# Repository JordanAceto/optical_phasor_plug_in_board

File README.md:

# NOTE: development of all VCF plug-in boards has been moved here https://github.com/JordanAceto/VCF_plug_in_boards

### This repo will no longer be updated. Follow the above link for the most current files.

# Optical Phasor Plug-In Board

Small 6 stage optical phase shifter PCB, designed to plug into a larger motherboard.

## Details

The main circuit is based on the famous Mutron phasor circuit with the addition of voltage controlled feedback. This PCB includes the audio path and CV inputs for frequency and feedback, but does not include any modulation sources.

The intended use for this board is to plug in to a larger motherboard which contains slots for two of these phasor boards, as well as modulation sources, panel controls, and input/output routing. This motherboard could accept different filter boards sharing this footprint and header layout, for realizing stereo effects of various flavors.

## Inputs

-Audio in: dry audio input to be phase shifted.

-Frequency CV in: 0 volts to +2.048 volts, higher voltage = higher sweep.

-Feedback CV in: 0 volts to +2.048 volts, higher voltage = more feedback.

## Outputs

-Audio out: phase shifted audio output.

## Power Supply Requirements

A bipolar 12 volt power supply capable of supplying 50mA is needed. This will typically come from the motherboard.

## Note About The Light Dependent Resistors

Low on resistance and high off resistance are desirable if a wide sweep range is wanted. Slow/fast response is up to personal taste.

The choice of LED has a large impact on sweep depth. Diffused green LEDs were found to produce good results, but feel free to experiment.

The LED and surrounding LDRs should be protected from ambient light under an opaque cover.

## Calibration

-RV1 (depth trim): trims the depth of incoming frequency CV signals. Turn CW for greater depth and CCW for less depth. Adjust to taste.

-RV2 (center trim): trims the center frequency of the phase shifter. Turn CW for higher center frequency and CCW for lower center frequency. Adjust to taste.

-RV3 (feedback trim): trims the maximum amount of feedback. Turn CW for more maximum feedback and CCW for less maximum feedback. Exercise caution when adjusting this, as extreme settings can result in loud oscillations which could damage your ears or speakers if you are monitoring the sound with a loud amplifier. If you set this trimmer to be right on the edge of oscillation when about +2 volts is applied to the feedback CV input then make sure to sweep the frequency through its entire range, as a setting that doesn't squeal at certain frequency settings may squeal at other settings.

## Parts Ordering
The BOM has a link to a Mouser project with the majority of the parts needed to build the board, with the exception of the LDRs. There is a link to the SmallBear Electronics parts page for their LDRs, which were found to work well. Feel free to experiment with different LDRs.

The BOM also has a link to OSHPark, where you can order boards. If a different PCB house is desired, gerbers and necessary files can be generated from the kicad_docs.

## License
CC by 4.0

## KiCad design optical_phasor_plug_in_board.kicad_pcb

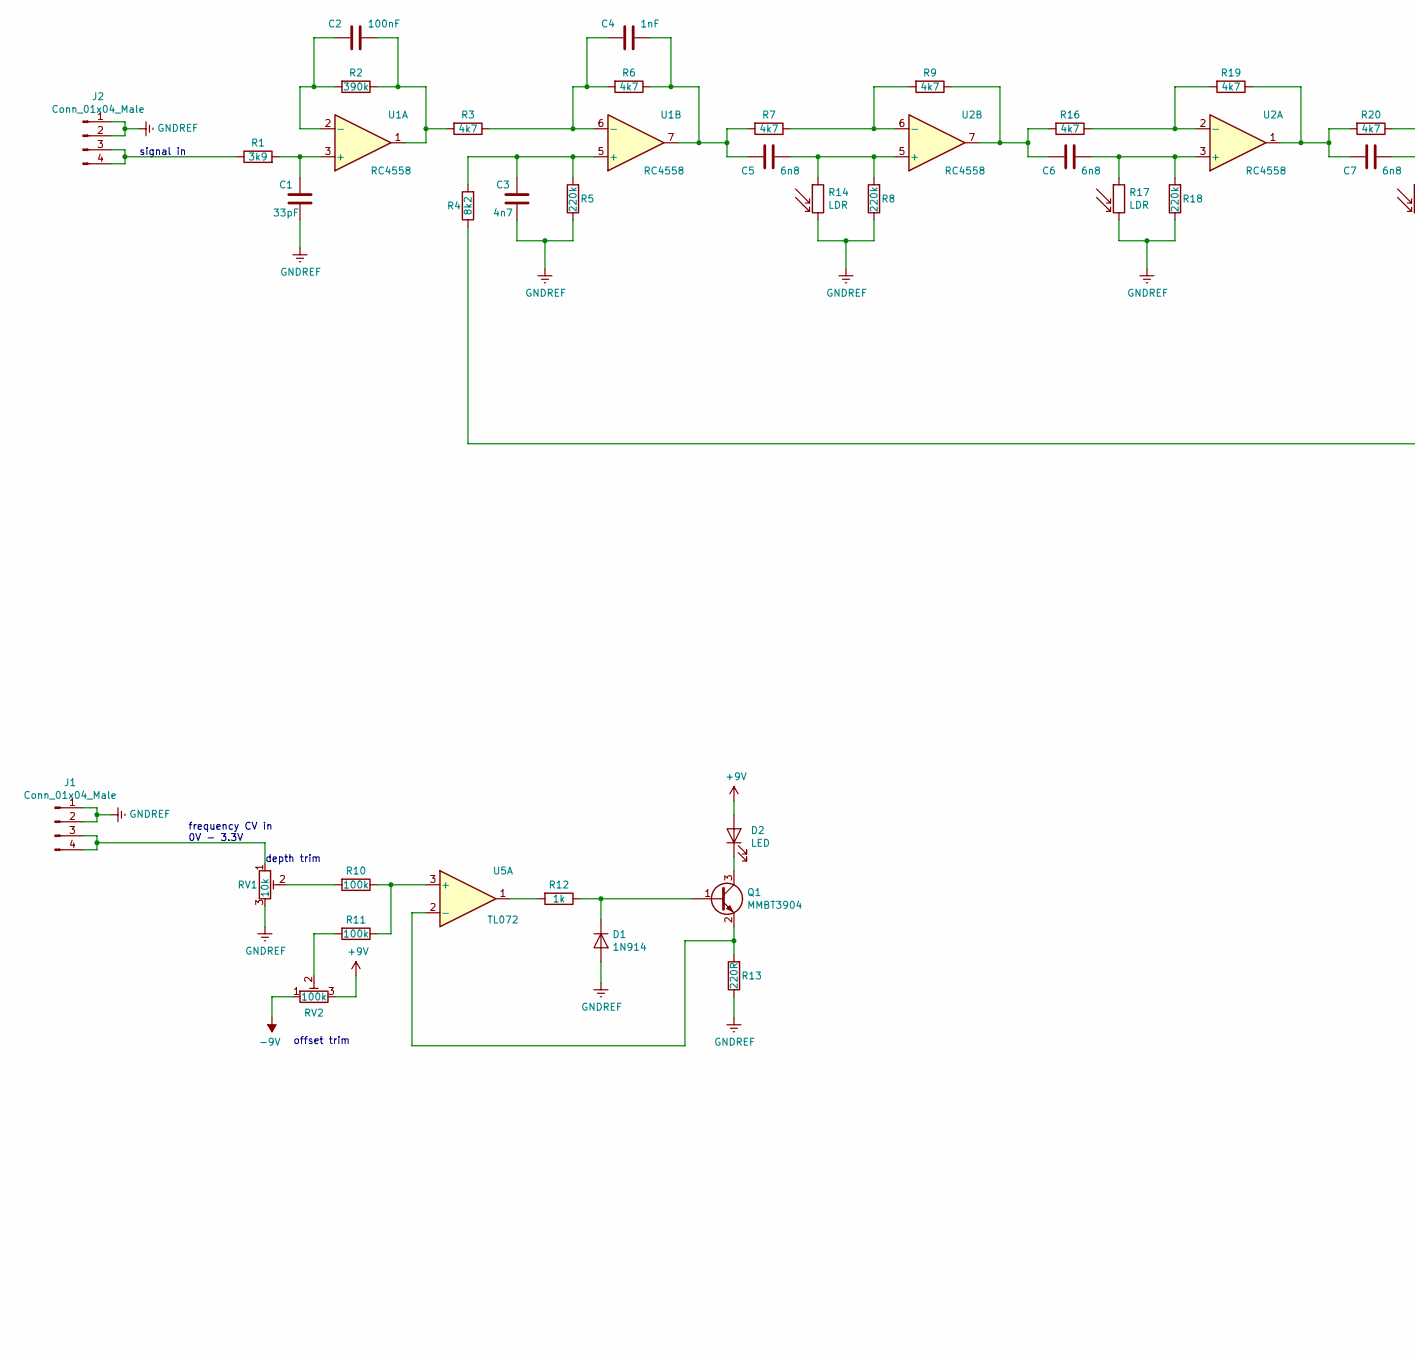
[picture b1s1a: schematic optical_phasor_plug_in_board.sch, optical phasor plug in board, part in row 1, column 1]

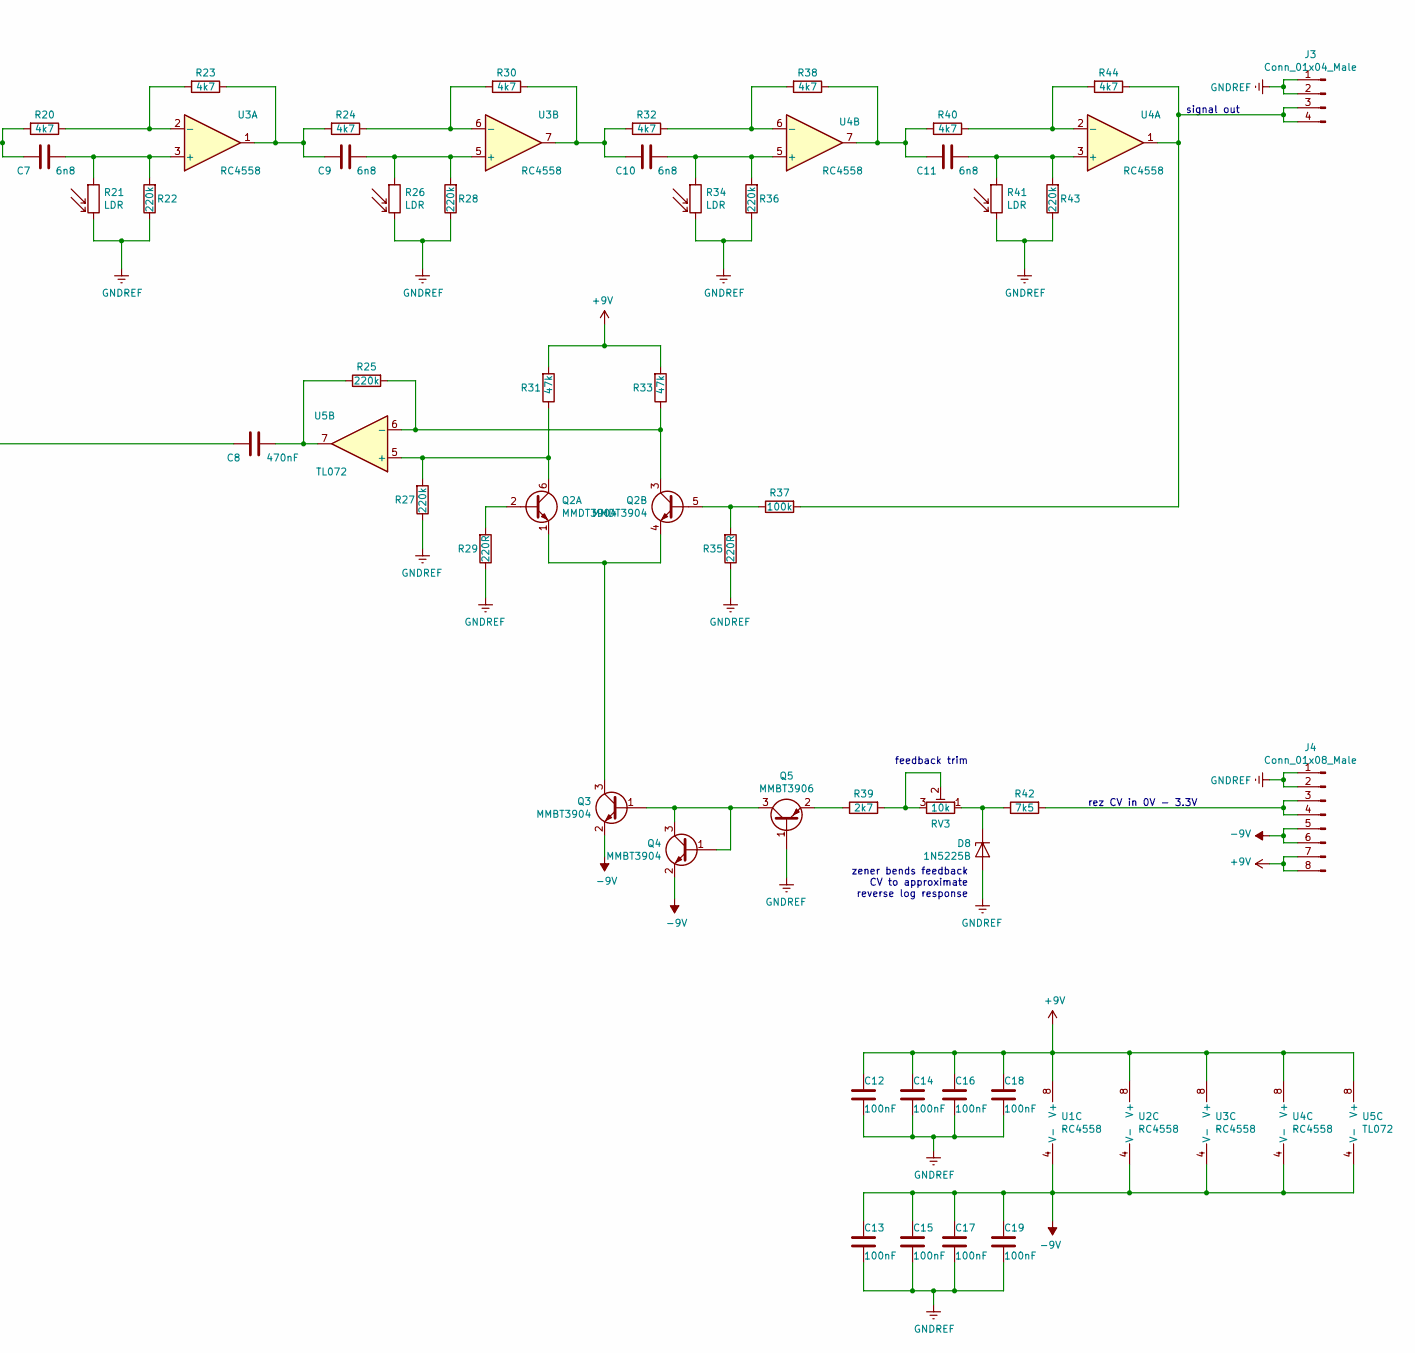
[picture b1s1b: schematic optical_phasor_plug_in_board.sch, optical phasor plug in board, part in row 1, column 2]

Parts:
C1: 33pF; C_0805_2012Metric_Pad1.15x1.40mm_HandSolder
C2, C12, C13, C14, C15, C16, C17, C18, C19: 100nF; C_0805_2012Metric_Pad1.15x1.40mm_HandSolder
C3: 4n7; C_0805_2012Metric_Pad1.15x1.40mm_HandSolder
C4: 1nF; C_0805_2012Metric_Pad1.15x1.40mm_HandSolder
C5, C6, C7, C9, C10, C11: 6n8; C_0805_2012Metric_Pad1.15x1.40mm_HandSolder
C8: 470nF; C_0805_2012Metric_Pad1.15x1.40mm_HandSolder
D1: 1N914; D_SOD-123
D2: LED; LED_D5.0mm
D8: 1N5225B; D_SOD-123
J1, J2, J3: Conn_01x04_Male; PinHeader_1x04_P2.54mm_Vertical
J4: Conn_01x08_Male; PinHeader_1x08_P2.54mm_Vertical
Q1, Q3, Q4: MMBT3904; SOT-23
Q2: MMDT3904; SOT-363_SC-70-6
Q5: MMBT3906; SOT-23
R1: 3k9; R_0805_2012Metric_Pad1.15x1.40mm_HandSolder
R2: 390k; R_0805_2012Metric_Pad1.15x1.40mm_HandSolder
R3, R6, R7, R9, R16, R19, R20, R23, R24, R30, R32, R38, R40, R44: 4k7; R_0805_2012Metric_Pad1.15x1.40mm_HandSolder
R4: 8k2; R_0805_2012Metric_Pad1.15x1.40mm_HandSolder
R5, R8, R18, R22, R25, R27, R28, R36, R43: 220k; R_0805_2012Metric_Pad1.15x1.40mm_HandSolder
R10, R11, R37: 100k; R_0805_2012Metric_Pad1.15x1.40mm_HandSolder
R12: 1k; R_0805_2012Metric_Pad1.15x1.40mm_HandSolder
R13, R29, R35: 220R; R_0805_2012Metric_Pad1.15x1.40mm_HandSolder
R14, R17, R21, R26, R34, R41: LDR; R_LDR_5.0x4.1mm_P3mm_Vertical
R31, R33: 47k; R_0805_2012Metric_Pad1.15x1.40mm_HandSolder
R39: 2k7; R_0805_2012Metric_Pad1.15x1.40mm_HandSolder
R42: 7k5; R_0805_2012Metric_Pad1.15x1.40mm_HandSolder
RV1, RV3: 10k; Potentiometer_Bourns_3296W_Vertical
RV2: 100k; Potentiometer_Bourns_3296W_Vertical
U1, U2, U3, U4: RC4558; SOIC-8_3.9x4.9mm_P1.27mm
U5: TL072; SOIC-8_3.9x4.9mm_P1.27mm

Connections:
+9V: C12.1, C14.1, C16.1, C18.1, D2.2 (A), J4.7, J4.8, R31.2, R33.2, RV2.3, U1.8 (V+), U2.8 (V+), U3.8 (V+), U4.8 (V+), U5.8 (V+)
-9V: C13.1, C15.1, C17.1, C19.1, J4.5, J4.6, Q3.2 (E), Q4.2 (E), RV2.1, U1.4 (V-), U2.4 (V-), U3.4 (V-), U4.4 (V-), U5.4 (V-)
GNDREF: C1.2, C3.2, C12.2, C13.2, C14.2, C15.2, C16.2, C17.2, C18.2, C19.2, D1.2 (A), D8.2 (A), J1.1, J1.2, J2.1, J2.2, J3.1, J3.2, J4.1, J4.2, Q5.1 (B), R5.1, R8.1, R13.1, R14.2, R17.2, R18.1, R21.2, R22.1, R26.2, R27.1, R28.1, R29.1, R34.2, R35.1, R36.1, R41.2, R43.1, RV1.3
unnamed: C1.1, R1.2, U1.3 (+)
unnamed: C2.1, R2.1, R3.2, U1.1
unnamed: C2.2, R2.2, U1.2 (-)
unnamed: C3.1, R4.2, R5.2, U1.5 (+)
unnamed: C4.1, R3.1, R6.2, U1.6 (-)
unnamed: C4.2, C5.2, R6.1, R7.2, U1.7
unnamed: C5.1, R8.2, R14.1, U2.5 (+)
unnamed: C6.1, R17.1, R18.2, U2.3 (+)
unnamed: C6.2, R9.1, R16.2, U2.7
unnamed: C7.1, R21.1, R22.2, U3.3 (+)
unnamed: C7.2, R19.1, R20.2, U2.1
unnamed: C8.1, R4.1
unnamed: C8.2, R25.1, U5.7
unnamed: C9.1, R26.1, R28.2, U3.5 (+)
unnamed: C9.2, R23.1, R24.2, U3.1
unnamed: C10.1, R34.1, R36.2, U4.5 (+)
unnamed: C10.2, R30.1, R32.2, U3.7
unnamed: C11.1, R41.1, R43.2, U4.3 (+)
unnamed: C11.2, R38.1, R40.2, U4.7
unnamed: D1.1 (K), Q1.1 (B), R12.1
unnamed: D2.1 (K), Q1.3 (C)
unnamed: D8.1 (K), R42.1, RV3.1
unnamed: J1.3, J1.4, RV1.1
unnamed: J2.3, J2.4, R1.1
unnamed: J3.3, J3.4, R37.2, R44.1, U4.1
unnamed: J4.3, J4.4, R42.2
unnamed: Q1.2 (E), R13.2, U5.2 (-)
unnamed: Q2.1 (E1), Q2.4 (E2), Q3.3 (C)
unnamed: Q2.2 (B1), R29.2
unnamed: Q2.3 (C2), R25.2, R33.1, U5.6 (-)
unnamed: Q2.5 (B2), R35.2, R37.1
unnamed: Q2.6 (C1), R27.2, R31.1, U5.5 (+)
unnamed: Q3.1 (B), Q4.1 (B), Q4.3 (C), Q5.3 (C)
unnamed: Q5.2 (E), R39.1
unnamed: R7.1, R9.2, U2.6 (-)
unnamed: R10.1, R11.1, U5.3 (+)
unnamed: R10.2, RV1.2
unnamed: R11.2, RV2.2
unnamed: R12.2, U5.1
unnamed: R16.1, R19.2, U2.2 (-)
unnamed: R20.1, R23.2, U3.2 (-)
unnamed: R24.1, R30.2, U3.6 (-)
unnamed: R32.1, R38.2, U4.6 (-)
unnamed: R39.2, RV3.2, RV3.3
unnamed: R40.1, R44.2, U4.2 (-)

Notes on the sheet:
offset trim
depth trim
zener bends feedback CV to approximate reverse log response
feedback trim
signal in
frequency CV in 0V - 3.3V
signal out
rez CV in 0V - 3.3V

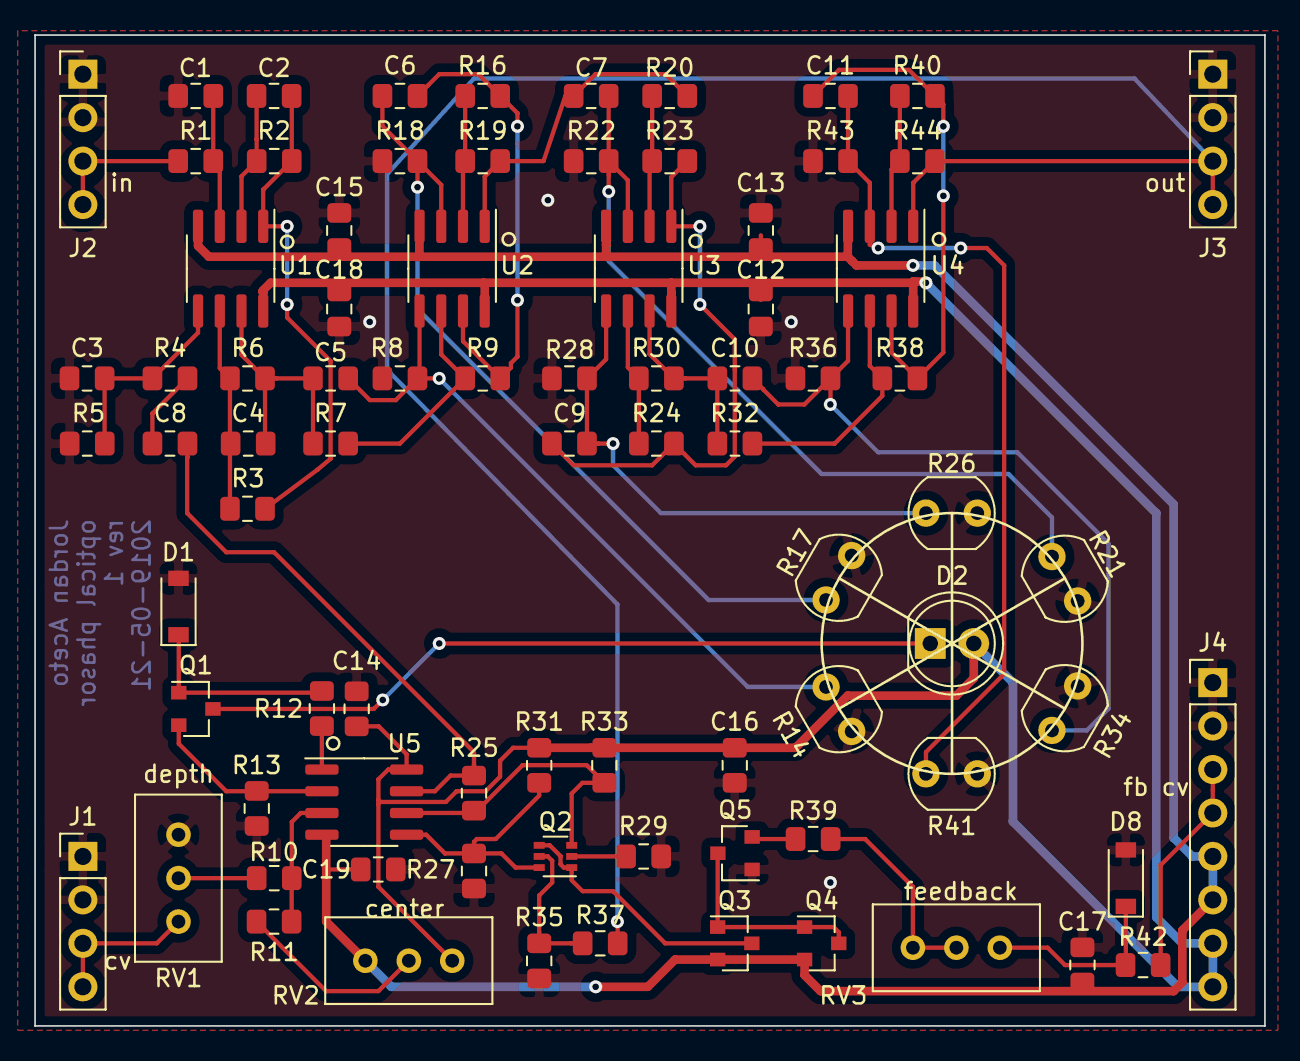
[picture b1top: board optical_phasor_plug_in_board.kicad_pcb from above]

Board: 2 copper layers, 71.9 x 57.9 mm, 82 parts (0 on the bottom side), 48 nets.

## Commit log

2019-05-22 add pdf of schematic
2019-05-22 add jpegs of rendered board front and back
2019-05-22 add link to mouser project in BOM
2019-05-24 rename BOM, change APF cap type in BOM
2019-05-24 fix mistake with BOM name
2019-05-28 add text file of potential improvements for next rev
2019-05-28 fix typo and clarify next rev improvements text file
2019-05-28 add to next rev notes
2019-06-04 rev 1.1
2019-06-04 add basic README.md
2019-06-04 add picture and flesh out README
2019-06-06 add link to OSHPark board in BOM, tidy up BOM
2019-06-07 add info about parts ordering to README
2019-06-07 tidy up BOM
2020-02-02 Create LICENSE
2020-08-01 update readme to incluse link to new repo

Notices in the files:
optical_phasor_plug_in_board.kicad_pcb:
Licinse: CC by 4.0
optical_phasor_plug_in_board.sch:
creativecommons.org/licenses/by/4.0
